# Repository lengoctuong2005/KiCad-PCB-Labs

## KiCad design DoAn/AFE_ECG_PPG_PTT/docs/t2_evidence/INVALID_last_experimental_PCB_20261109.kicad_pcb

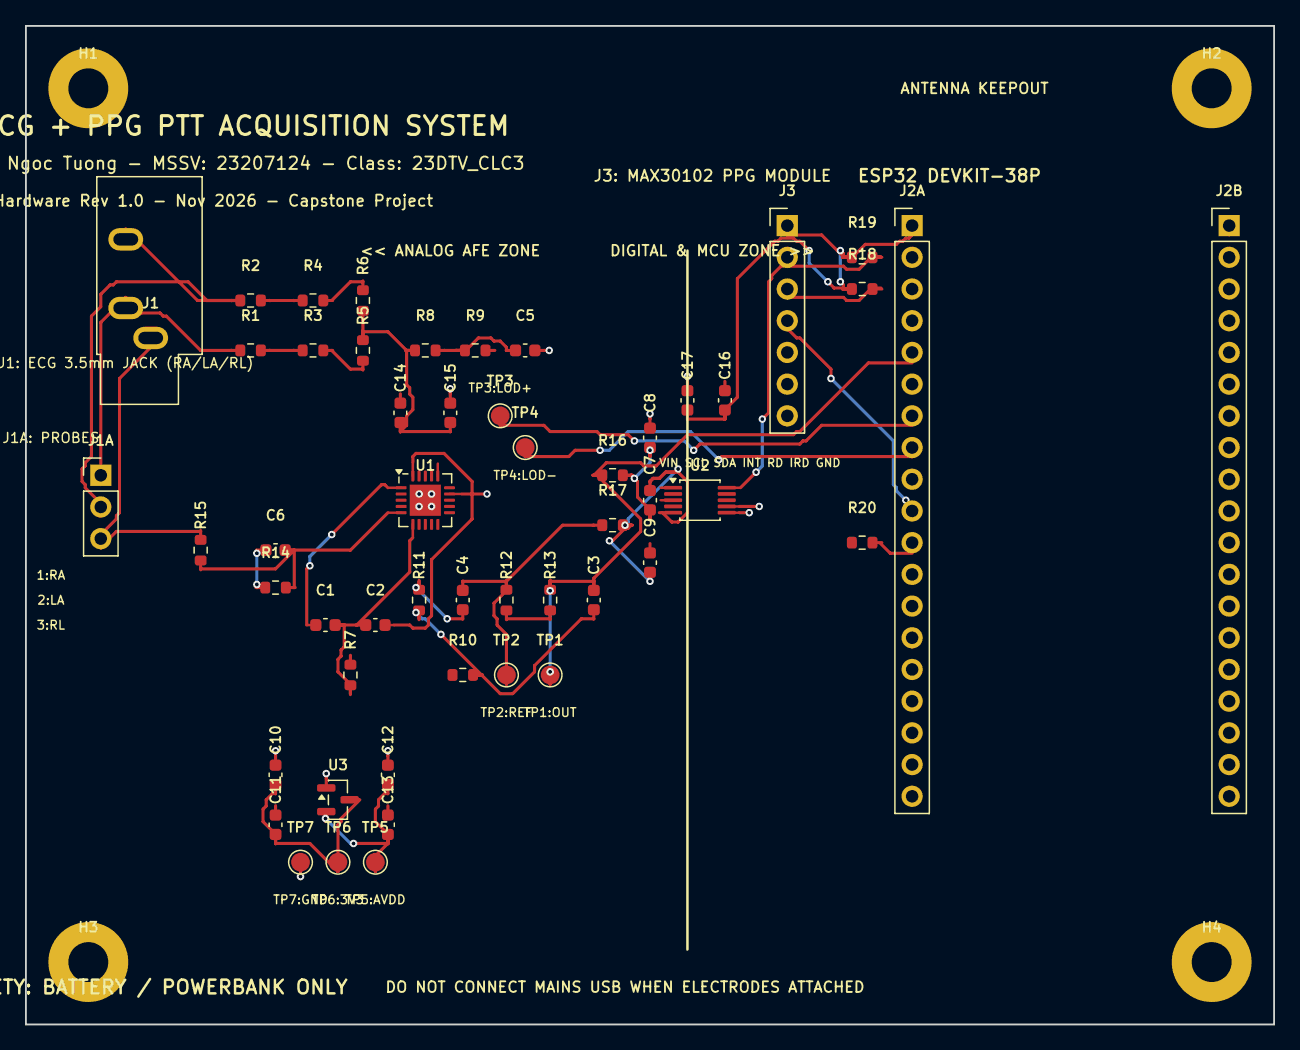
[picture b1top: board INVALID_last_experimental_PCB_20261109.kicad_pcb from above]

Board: 2 copper layers, 100.0 x 80.0 mm, 56 parts (0 on the bottom side), 31 nets.

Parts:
C1, C2: 0.33uF; C_0603_1608Metric
C3: 22nF; C_0603_1608Metric
C4, C7: 10nF; C_0603_1608Metric
C5, C11, C13, C14, C16: 0.1uF; C_0603_1608Metric
C6, C8, C9: 1nF; C_0603_1608Metric
C10, C12, C15, C17: 1uF; C_0603_1608Metric
H1, H2, H3, H4: M3; MountingHole_3.2mm_M3_Pad
J1: SJ1-3533NG; Jack_3.5mm_CUI_SJ1-3533NG_Horizontal
J1A: ECG_PROBES; PinHeader_1x03_P2.54mm_Vertical
J2A: ESP32_L; PinHeader_1x19_P2.54mm_Vertical
J2B: ESP32_R; PinHeader_1x19_P2.54mm_Vertical
J3: MAX30102; PinHeader_1x07_P2.54mm_Vertical
R1, R2, R3, R4: 180k; R_0603_1608Metric
R5, R6, R7, R8, R9: 10M; R_0603_1608Metric
R10, R11, R12: 100k; R_0603_1608Metric
R13, R14: 1M; R_0603_1608Metric
R15: 360k; R_0603_1608Metric
R16, R17: 1k; R_0603_1608Metric
R18, R19: 4.7k; R_0603_1608Metric
R20: 10k; R_0603_1608Metric
TP1: ECG_OUT; TestPoint_Pad_D1.5mm
TP2: REFOUT; TestPoint_Pad_D1.5mm
TP3: LOD+; TestPoint_Pad_D1.5mm
TP4: LOD-; TestPoint_Pad_D1.5mm
TP5: +VS_A; TestPoint_Pad_D1.5mm
TP6: +3V3; TestPoint_Pad_D1.5mm
TP7: GND; TestPoint_Pad_D1.5mm
U1: AD8232ACPZ; LFCSP-20-1EP_4x4mm_P0.5mm_EP2.5x2.5mm
U2: ADS1115IDGST; TSSOP-10_3x3mm_P0.5mm
U3: MCP1700-3002E; SOT-23

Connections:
+3V3: C10.1, C11.1, C16.1, C17.1, J2A.1, J3.1, R18.1, R19.1, R20.1, TP6.1, U2.8, U3.3
+VS_A: C12.1, C13.1, C14.1, C15.1, R5.1, R6.1, R8.1, TP5.1, U1.13, U1.17, U3.2
ADS_ALERT: J2A.11, R20.2, U2.2
AIN0_FILT: C7.1, C8.1, R16.2, U2.4
AIN1_FILT: C7.2, C9.1, R17.2, U2.5
ECG_OUT: C3.2, J2A.5, R13.2, R16.1, TP1.1, U1.10
FR: J2A.9, U1.15
GND: C5.2, C8.2, C9.2, C10.2, C11.2, C12.2, C13.2, C14.2, C15.2, C16.2, C17.2, H1.1, H2.1, H3.1, H4.1, J2A.14, J2B.1, J2B.7, J3.7, R7.2, R9.2, TP7.1, U1.14, U1.16, U1.21, U2.1, U2.3, U2.6, U2.7, U3.1
HPDRIVE: C1.1, U1.1
HPSENSE: C2.2, U1.20
HP_MID: C1.2, C2.1, R7.1, U1.6
I2C_SCL: J2B.3, J3.2, R19.2, U2.10
I2C_SDA: J2B.6, J3.3, R18.2, U2.9
IAOUT: R10.1, U1.19
LA_FILT: R4.2, R6.2, U1.3
LA_INT: R2.2, R4.1
LA_RAW: J1.R, J1A.2, R2.1
LOD+: J2A.7, TP3.1, U1.12
LOD-: J2A.8, TP4.1, U1.11
MAX_INT: J2A.10, J3.4
OPAMP_N: R12.1, R13.1, U1.9
OPAMP_P: C4.1, R11.2, U1.7
RA_FILT: R3.2, R5.2, U1.2
RA_INT: R1.2, R3.1
RA_RAW: J1.T, J1A.1, R1.1
REFIN: C5.1, R8.2, R9.1, U1.18
REFOUT: C4.2, R12.2, R17.1, TP2.1, U1.8
RLDFB: C6.1, R14.1, U1.4
RLD_OUT: C6.2, R14.2, R15.1, U1.5
RL_RAW: J1.S, J1A.3, R15.2
SK_N1: C3.1, R10.2, R11.1

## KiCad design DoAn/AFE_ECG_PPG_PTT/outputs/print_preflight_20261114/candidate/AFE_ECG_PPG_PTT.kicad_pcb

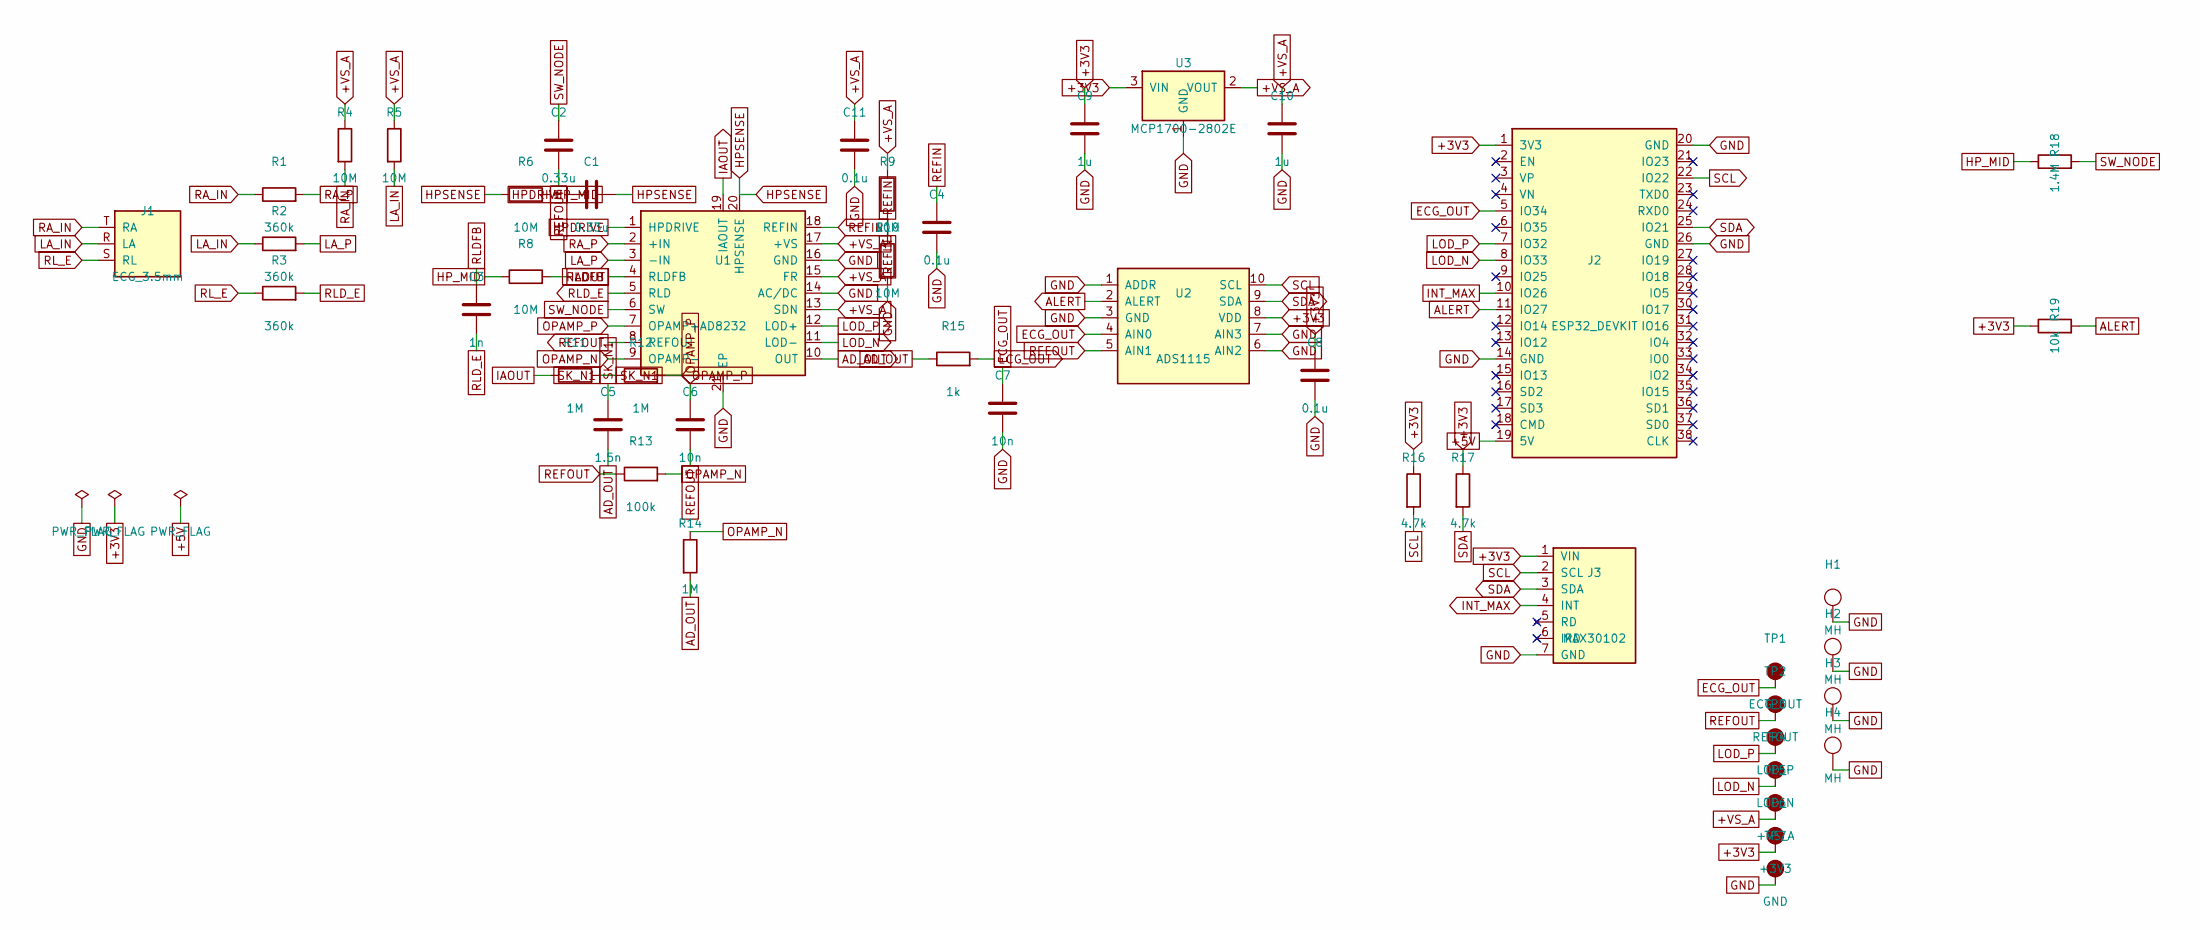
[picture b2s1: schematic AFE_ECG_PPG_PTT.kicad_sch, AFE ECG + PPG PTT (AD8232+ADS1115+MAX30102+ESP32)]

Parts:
C1, C2: 0.33u; C_0603_1608Metric
C3: 1n; C_0603_1608Metric
C4, C8, C11: 0.1u; C_0603_1608Metric
C5: 1.5n; C_0603_1608Metric
C6, C7: 10n; C_0603_1608Metric
C9, C10: 1u; C_0603_1608Metric
H1, H2, H3, H4: MH; MountingHole_3.2mm_M3_Pad
J1: ECG_3.5mm; Jack_3.5mm_CUI_SJ1-3533NG_Horizontal
J2: ESP32_DEVKIT; ESP32_DevKitC_V4_38P
J3: MAX30102; PinHeader_1x07_P2.54mm_Vertical
R1, R2, R3: 360k; R_0603_1608Metric
R4, R5, R6, R8, R9, R10: 10M; R_0603_1608Metric
R11, R12, R14: 1M; R_0603_1608Metric
R13: 100k; R_0603_1608Metric
R15: 1k; R_0603_1608Metric
R16, R17: 4.7k; R_0603_1608Metric
R18: 1.4M; R_0603_1608Metric
R19: 10k; R_0603_1608Metric
TP1: ECG_OUT; TestPoint_Pad_D1.5mm
TP2: REFOUT; TestPoint_Pad_D1.5mm
TP3: LOD_P; TestPoint_Pad_D1.5mm
TP4: LOD_N; TestPoint_Pad_D1.5mm
TP5: +VS_A; TestPoint_Pad_D1.5mm
TP6: +3V3; TestPoint_Pad_D1.5mm
TP7: GND; TestPoint_Pad_D1.5mm
U1: AD8232; LFCSP-20-1EP_4x4mm_P0.5mm_EP2.6x2.6mm
U2: ADS1115; TSSOP-10_3x3mm_P0.5mm
U3: MCP1700-2802E; SOT-23

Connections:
+3V3: C8.1, C9.1, J2.1 (3V3), J3.1 (VIN), R16.1, R17.1, R19.1, TP6.1, U2.8 (VDD), U3.3 (VIN)
+5V: J2.19 (5V)
+VS_A: C10.1, C11.1, R4.1, R5.1, R9.1, TP5.1, U1.13 (SDN), U1.15 (FR), U1.17 (+VS), U3.2 (VOUT)
AD_OUT: C5.2, R14.2, R15.1, U1.10 (OUT)
ALERT: J2.11 (IO27), R19.2, U2.2 (ALERT)
ECG_OUT: C7.1, J2.5 (IO34), R15.2, TP1.1, U2.4 (AIN0)
GND: C4.2, C7.2, C8.2, C9.2, C10.2, C11.2, H1.1, H2.1, H3.1, H4.1, J2.14 (GND), J2.20 (GND), J2.26 (GND), J3.7 (GND), R10.2, TP7.1, U1.14 (AC/DC), U1.16 (GND), U1.21 (EP), U2.1 (ADDR), U2.3 (GND), U2.6 (AIN2), U2.7 (AIN3), U3.1 (GND)
HPDRIVE: C1.1, U1.1 (HPDRIVE)
HPSENSE: C1.2, R6.1, U1.20 (HPSENSE)
HP_MID: R6.2, R8.1, R18.1
IAOUT: R8.2, R11.1, U1.19 (IAOUT)
INT_MAX: J2.10 (IO26), J3.4 (INT)
LA_IN: J1.R (LA), R2.1, R5.2
LA_P: R2.2, U1.3 (-IN)
LOD_N: J2.8 (IO33), TP4.1, U1.11 (LOD-)
LOD_P: J2.7 (IO32), TP3.1, U1.12 (LOD+)
OPAMP_N: R13.2, R14.1, U1.9 (OPAMP-)
OPAMP_P: C6.1, R12.2, U1.7 (OPAMP+)
RA_IN: J1.T (RA), R1.1, R4.2
RA_P: R1.2, U1.2 (+IN)
REFIN: C4.1, R9.2, R10.1, U1.18 (REFIN)
REFOUT: C2.2, C6.2, R13.1, TP2.1, U1.8 (REFOUT), U2.5 (AIN1)
RLDFB: C3.1, U1.4 (RLDFB)
RLD_E: C3.2, R3.2, U1.5 (RLD)
RL_E: J1.S (RL), R3.1
SCL: J2.22 (IO22), J3.2 (SCL), R16.2, U2.10 (SCL)
SDA: J2.25 (IO21), J3.3 (SDA), R17.2, U2.9 (SDA)
SK_N1: C5.1, R11.2, R12.1
SW_NODE: C2.1, R18.2, U1.6 (SW)

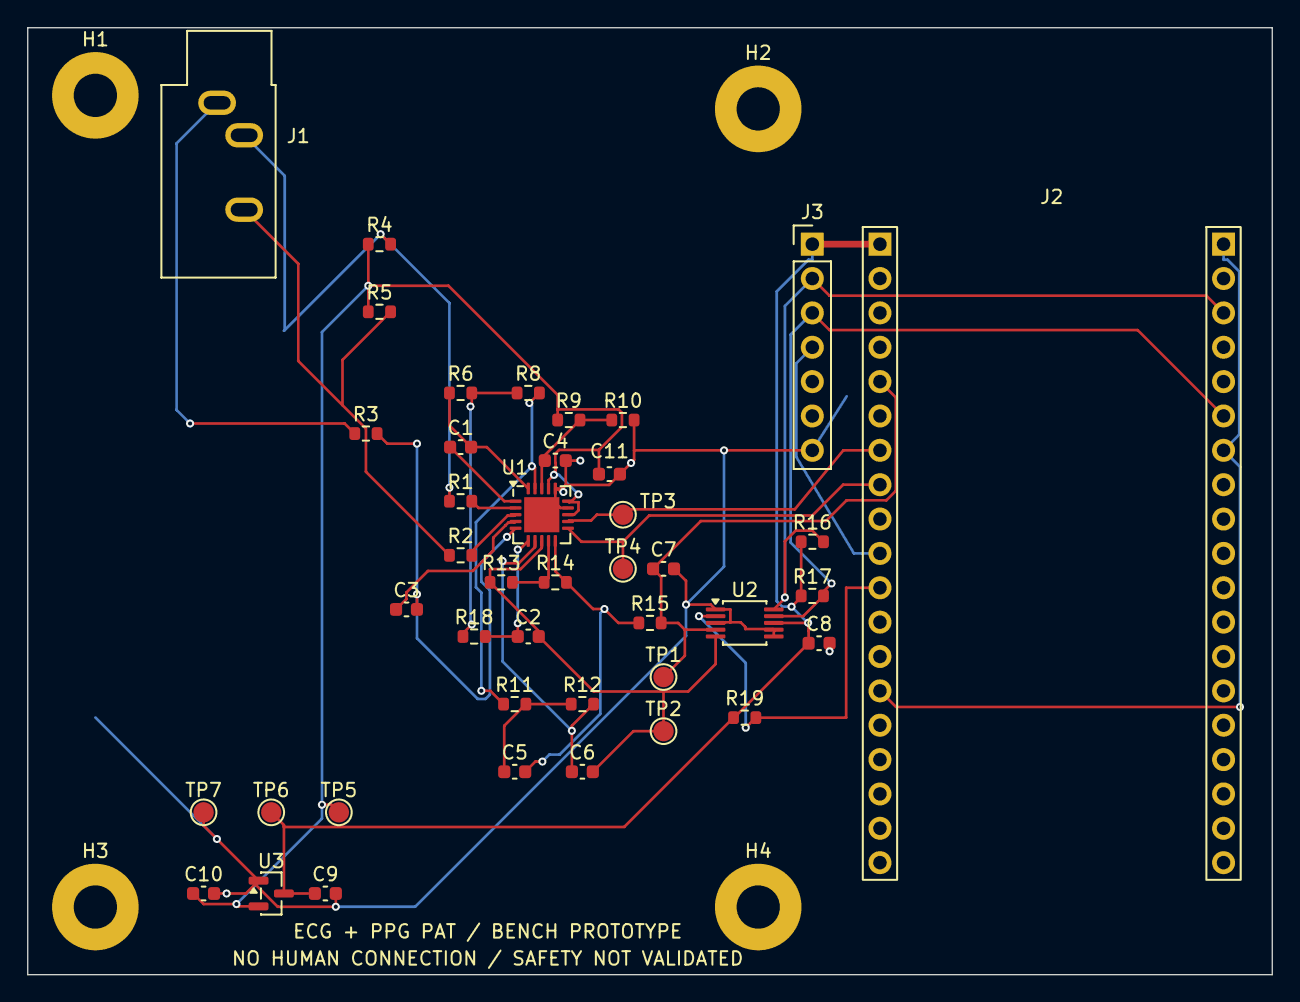
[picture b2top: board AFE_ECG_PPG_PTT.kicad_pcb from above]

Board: 2 copper layers, 92.0 x 70.0 mm, 46 parts (0 on the bottom side), 28 nets.

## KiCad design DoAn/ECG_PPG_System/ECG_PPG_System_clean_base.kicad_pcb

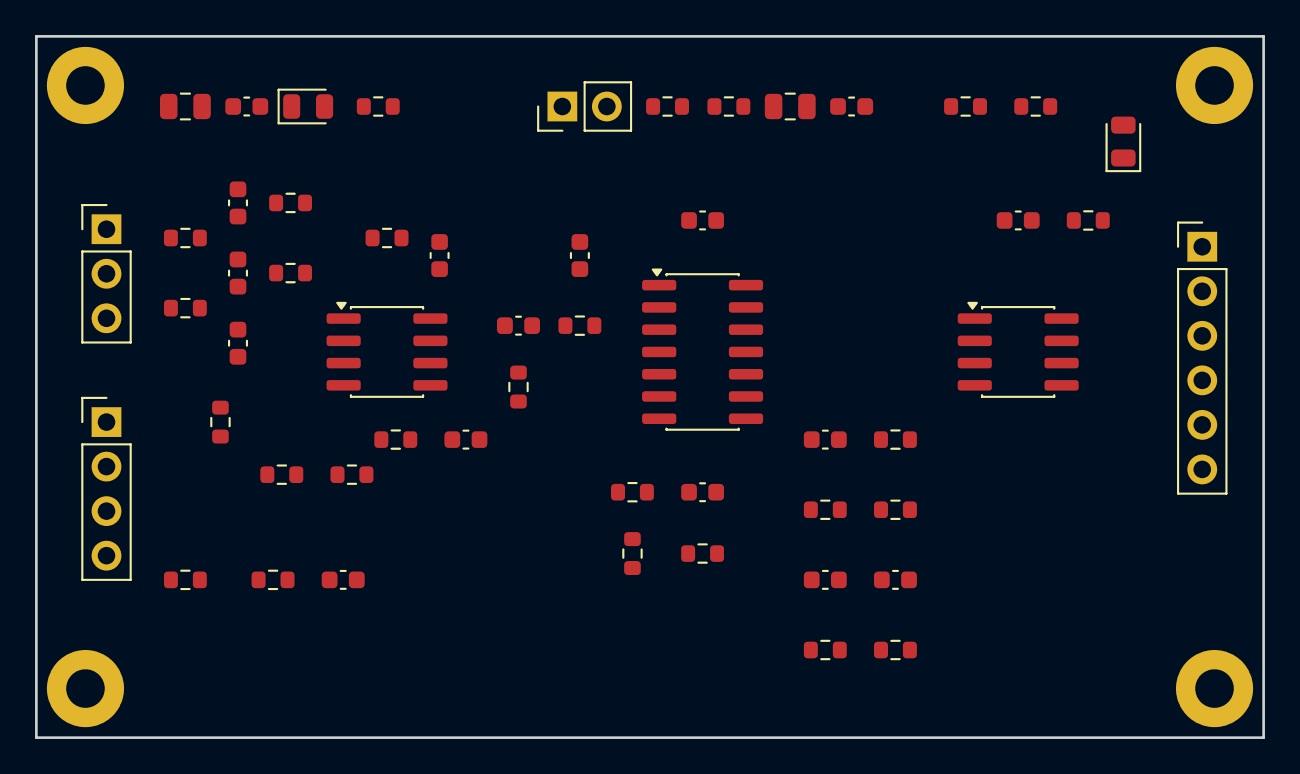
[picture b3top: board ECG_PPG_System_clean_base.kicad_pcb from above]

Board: 2 copper layers, 70.0 x 40.0 mm, 58 parts (0 on the bottom side), 31 nets, no tracks yet.

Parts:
C1, C3: 10uF; C_0805_2012Metric
C2, C4, C8, C11, C13, C18: 100nF; C_0603_1608Metric
C5: 100pF; C_0603_1608Metric
C6, C7: 47pF; C_0603_1608Metric
C9: 1nF; C_0603_1608Metric
C10, C15, C16: 1uF; C_0603_1608Metric
C12: 47nF; C_0603_1608Metric
C14: 22pF; C_0603_1608Metric
C17: 470nF; C_0603_1608Metric
D1: Green_PWR; LED_0805_2012Metric
D2: Red_PULSE; LED_0805_2012Metric
H1, H2, H3, H4: M2; MountingHole_2.2mm_M2_Pad
J1: Power_In; PinHeader_1x02_P2.54mm_Vertical
J2: ECG_Leads; PinHeader_1x03_P2.54mm_Vertical
J3: PPG_Sensor; PinHeader_1x04_P2.54mm_Vertical
J4: System_Out; PinHeader_1x06_P2.54mm_Vertical
R1, R2, R9, R10, R25: 100k; R_0603_1608Metric
R3, R4, R5, R8, R23, R27: 1k; R_0603_1608Metric
R6, R7: 10M; R_0603_1608Metric
R11, R18: 1M; R_0603_1608Metric
R12: 390k; R_0603_1608Metric
R13, R20: 330k; R_0603_1608Metric
R14, R15: 39k; R_0603_1608Metric
R16, R26: 10k; R_0603_1608Metric
R17: 91k; R_0603_1608Metric
R19: 220R; R_0603_1608Metric
R21, R22: 15k; R_0603_1608Metric
R24: 47k; R_0603_1608Metric
U1: AD623ARZ; SOIC-8_3.9x4.9mm_P1.27mm
U2: MCP6004-E/SL; SOIC-14_3.9x8.7mm_P1.27mm
U3: MCP6002-E/SN; SOIC-8_3.9x4.9mm_P1.27mm

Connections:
DRL_CM: C9.1, R9.2, R10.2, R11.1, U2.5
DRL_OUT: C9.2, R11.2, R12.1, U2.7
ECG_FB: R16.1, R17.1, U2.9
ECG_HPF_OUT: C10.2, R13.1, R14.1
ECG_IA_OUT: C10.1, U1.6
ECG_LPF_IN: C12.1, R15.2, U2.10
ECG_LPF_NODE: C11.1, R14.2, R15.1
ECG_OUT: C11.2, J4.3, R17.2, U2.8
GND: C1.2, C2.2, C3.2, C4.2, C6.2, C7.2, C8.2, C13.2, C18.2, D1.1, D2.1, H1.1, H2.1, H3.1, H4.1, J1.2, J3.4, J4.2, R2.2, R26.2, U1.4, U2.11, U3.4
LA_FILT: C5.2, C7.1, R5.2, R7.1, R10.1, U1.3
LA_RAW: J2.2, R5.1
LED_DRV: J3.2, R19.2
NET_D1_R3: D1.2, R3.2
NET_D2_R27: D2.2, R27.2
PD_ANODE: C14.1, J3.3, R18.1, U2.12
PPG_FB: R23.1, R24.1, U3.2
PPG_HPF_OUT: C15.2, R20.1, R21.1
PPG_LPF_IN: C17.1, R22.2, U3.3
PPG_LPF_NODE: C16.1, R21.2, R22.1
PPG_OUT: C16.2, J4.4, R24.2, U3.1, U3.5
PPG_TIA_OUT: C14.2, C15.1, R18.2, U2.14
PULSE_TRIG: J4.5, R27.1, U3.7
RA_FILT: C5.1, C6.1, R4.2, R6.1, R9.1, U1.2
RA_RAW: J2.1, R4.1
RG1: R8.1, U1.1
RG2: R8.2, U1.8
RL_DRL: J2.3, R12.2
VCC: C1.1, C2.1, C8.1, C13.1, C18.1, J1.1, J3.1, J4.1, R1.1, R3.1, R19.1, U1.7, U2.4, U3.8
VMID: C3.1, C4.1, R1.2, R2.1, U2.3
VREF: C12.2, C17.2, J4.6, R6.2, R7.2, R13.2, R16.2, R20.2, R23.2, R25.1, U1.5, U2.1, U2.2, U2.6, U2.13
VREF_THR: R25.2, R26.1, U3.6

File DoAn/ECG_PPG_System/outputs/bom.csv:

"Refs","Value","Footprint","Qty","DNP"
"C1","10uF","Capacitor_SMD:C_0805_2012Metric","1",""
"C2","100nF","Capacitor_SMD:C_0603_1608Metric","1",""
"C3","10uF","Capacitor_SMD:C_0805_2012Metric","1",""
"C4","100nF","Capacitor_SMD:C_0603_1608Metric","1",""
"C5","100pF","Capacitor_SMD:C_0603_1608Metric","1",""
"C6","47pF","Capacitor_SMD:C_0603_1608Metric","1",""
"C7","47pF","Capacitor_SMD:C_0603_1608Metric","1",""
"C8","100nF","Capacitor_SMD:C_0603_1608Metric","1",""
"C9","1nF","Capacitor_SMD:C_0603_1608Metric","1",""
"C10","1uF","Capacitor_SMD:C_0603_1608Metric","1",""
"C11","100nF","Capacitor_SMD:C_0603_1608Metric","1",""
"C12","47nF","Capacitor_SMD:C_0603_1608Metric","1",""
"C13","100nF","Capacitor_SMD:C_0603_1608Metric","1",""
"C14","22pF","Capacitor_SMD:C_0603_1608Metric","1",""
"C15","1uF","Capacitor_SMD:C_0603_1608Metric","1",""
"C16","1uF","Capacitor_SMD:C_0603_1608Metric","1",""
"C17","470nF","Capacitor_SMD:C_0603_1608Metric","1",""
"C18","100nF","Capacitor_SMD:C_0603_1608Metric","1",""
"D1","Green_PWR","LED_SMD:LED_0805_2012Metric","1",""
"D2","Red_PULSE","LED_SMD:LED_0805_2012Metric","1",""
"J1","Power_In","Connector_PinHeader_2.54mm:PinHeader_1x02_P2.54mm_Vertical","1",""
"J2","ECG_Leads","Connector_PinHeader_2.54mm:PinHeader_1x03_P2.54mm_Vertical","1",""
"J3","PPG_Sensor","Connector_PinHeader_2.54mm:PinHeader_1x04_P2.54mm_Vertical","1",""
"J4","System_Out","Connector_PinHeader_2.54mm:PinHeader_1x06_P2.54mm_Vertical","1",""
"R1","100k","Resistor_SMD:R_0603_1608Metric","1",""
"R2","100k","Resistor_SMD:R_0603_1608Metric","1",""
"R3","1k","Resistor_SMD:R_0603_1608Metric","1",""
"R4","1k","Resistor_SMD:R_0603_1608Metric","1",""
"R5","1k","Resistor_SMD:R_0603_1608Metric","1",""
"R6","10M","Resistor_SMD:R_0603_1608Metric","1",""
"R7","10M","Resistor_SMD:R_0603_1608Metric","1",""
"R8","1k","Resistor_SMD:R_0603_1608Metric","1",""
"R9","100k","Resistor_SMD:R_0603_1608Metric","1",""
"R10","100k","Resistor_SMD:R_0603_1608Metric","1",""
"R11","1M","Resistor_SMD:R_0603_1608Metric","1",""
"R12","390k","Resistor_SMD:R_0603_1608Metric","1",""
"R13","330k","Resistor_SMD:R_0603_1608Metric","1",""
"R14","39k","Resistor_SMD:R_0603_1608Metric","1",""
"R15","39k","Resistor_SMD:R_0603_1608Metric","1",""
"R16","10k","Resistor_SMD:R_0603_1608Metric","1",""
"R17","91k","Resistor_SMD:R_0603_1608Metric","1",""
"R18","1M","Resistor_SMD:R_0603_1608Metric","1",""
"R19","220R","Resistor_SMD:R_0603_1608Metric","1",""
"R20","330k","Resistor_SMD:R_0603_1608Metric","1",""
"R21","15k","Resistor_SMD:R_0603_1608Metric","1",""
"R22","15k","Resistor_SMD:R_0603_1608Metric","1",""
"R23","1k","Resistor_SMD:R_0603_1608Metric","1",""
"R24","47k","Resistor_SMD:R_0603_1608Metric","1",""
"R25","100k","Resistor_SMD:R_0603_1608Metric","1",""
"R26","10k","Resistor_SMD:R_0603_1608Metric","1",""
"R27","1k","Resistor_SMD:R_0603_1608Metric","1",""
"U1","AD623ARZ","Package_SO:SOIC-8_3.9x4.9mm_P1.27mm","1",""
"U2","MCP6004-E/SL","Package_SO:SOIC-14_3.9x8.7mm_P1.27mm","1",""
"U3","MCP6002-E/SN","Package_SO:SOIC-8_3.9x4.9mm_P1.27mm","1",""

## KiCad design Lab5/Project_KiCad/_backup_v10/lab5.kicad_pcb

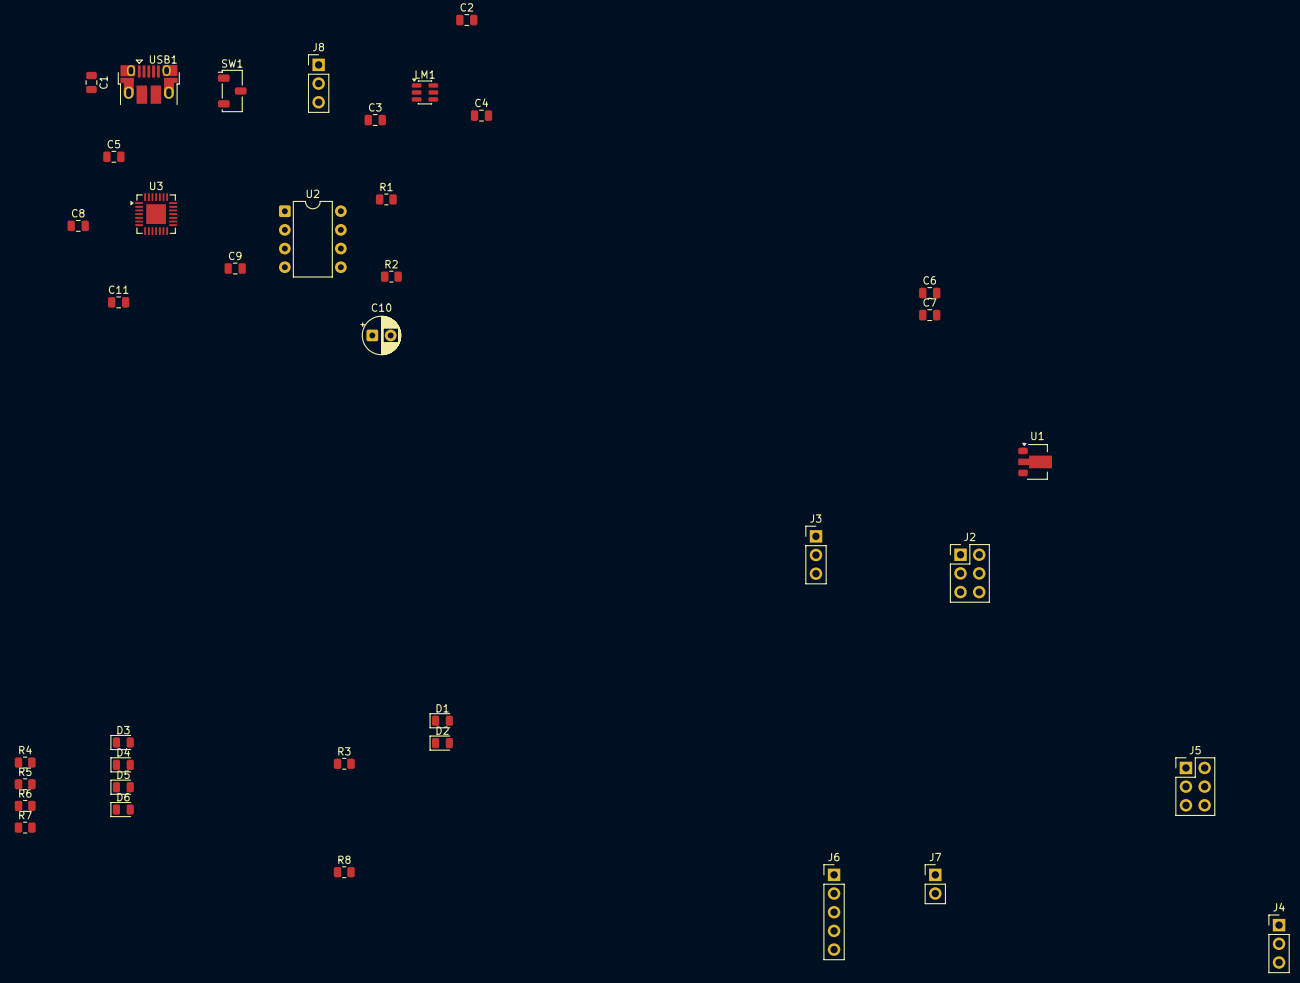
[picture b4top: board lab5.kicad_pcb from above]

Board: 2 copper layers, 38 parts (0 on the bottom side), 29 nets, no tracks yet.

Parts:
C1, C2, C3, C6, C7: 2.2uF; C_0805_2012Metric
C4: 1uF; C_0805_2012Metric
C5, C8, C11: 100nF; C_0805_2012Metric
C9: 10nF; C_0805_2012Metric
C10: 10uF; CP_Radial_D5.0mm_P2.50mm
D1: TX1; LED_0805_2012Metric
D2: RX1; LED_0805_2012Metric
D3: 5V; LED_0805_2012Metric
D4: 3V3; LED_0805_2012Metric
D5: -VDD; LED_0805_2012Metric
D6: 1Hz; LED_0805_2012Metric
J2, J5: Connector 3x2; PinHeader_2x03_P2.54mm_Vertical
J3, J4: Jumper_Dual_1x3; PinHeader_1x03_P2.54mm_Vertical
J6: Connector_1x5; PinHeader_1x05_P2.54mm_Vertical
J7: Connector_1x2; PinHeader_1x02_P2.54mm_Vertical
J8: Conn_01x03; PinHeader_1x03_P2.54mm_Vertical
LM1: SOT-23-6
R1: 47k; R_0805_2012Metric
R2: 100k; R_0805_2012Metric
R3, R4, R5, R6, R7, R8: 1k; R_0805_2012Metric
SW1: ON/OFF SWITCH; Nidec_Copal_CAS-120A
U1: AMS1117-3V3; SOT-89-3
U2: NE555; DIP-8_W7.62mm
U3: CP2102; QFN-28-1EP_5x5mm_P0.5mm_EP2.7x2.7mm
USB1: USB_Micro-B_Amphenol_10103594-0001LF_Horizontal

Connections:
/1Hz: J7.2, R7.2, U2.3 (Q)
/D+: U3.4 (D+), USB1.3 (D+/DM)
/D-: U3.5 (D-), USB1.2 (D-/DM)
/DTR: C5.1, J6.4
/P1+: J2.1, J2.2, J2.3, J3.2
/P1-: J2.4, J2.5, J2.6
/P2+: J4.2, J5.1, J5.2, J5.3
/P2-: J5.4, J5.5, J5.6
/RX: D2.1 (K), J6.2, U3.25 (RXD)
/TX: D1.1 (K), J6.3, U3.26 (TXD)
/VDD_3V3: C7.2, J3.3, J4.3, J6.1, R5.2, U1.2 (Vout)
/VDD_5V: C6.2, C11.2, J3.1, J4.1, R1.1, R3.1, R4.2, R8.1, SW1.2, U1.3 (Vin), U2.4 (R), U2.8 (VCC), U3.7 (REGIN), U3.8 (VBUS)
GND: C1.2, C2.2, C3.2, C6.1, C7.1, C8.1, C9.2, C10.2, C11.1, D3.1 (K), D4.1 (K), D5.2 (A), D6.1 (K), J6.5, J7.1, LM1.2 (GND), U1.1, U2.1 (GND), U3.3 (GND), USB1.5 (GND), USB1.6
unnamed: D1.2 (A), R3.2
unnamed: D2.2 (A), R8.2
unnamed: D3.2 (A), R4.1
unnamed: D4.2 (A), R5.1
unnamed: D5.1 (K), R6.1
unnamed: D6.2 (A), R7.1
unnamed: C3.1, J8.2, LM1.4 (EN)
unnamed: C4.2, LM1.5 (C1+)
unnamed: C4.1, LM1.6 (C1-)
unnamed: C2.1, LM1.1 (VOUT)
unnamed: C9.1, U2.5 (CV)
unnamed: R1.2, R2.1, U2.7 (DC)
unnamed: C10.1, R2.2, U2.2 (TR), U2.6 (TH)
unnamed: C5.2, U3.28 (DTR)
unnamed: C8.2, U3.6 (VDD)
unnamed: C1.1, USB1.1 (VBUS)

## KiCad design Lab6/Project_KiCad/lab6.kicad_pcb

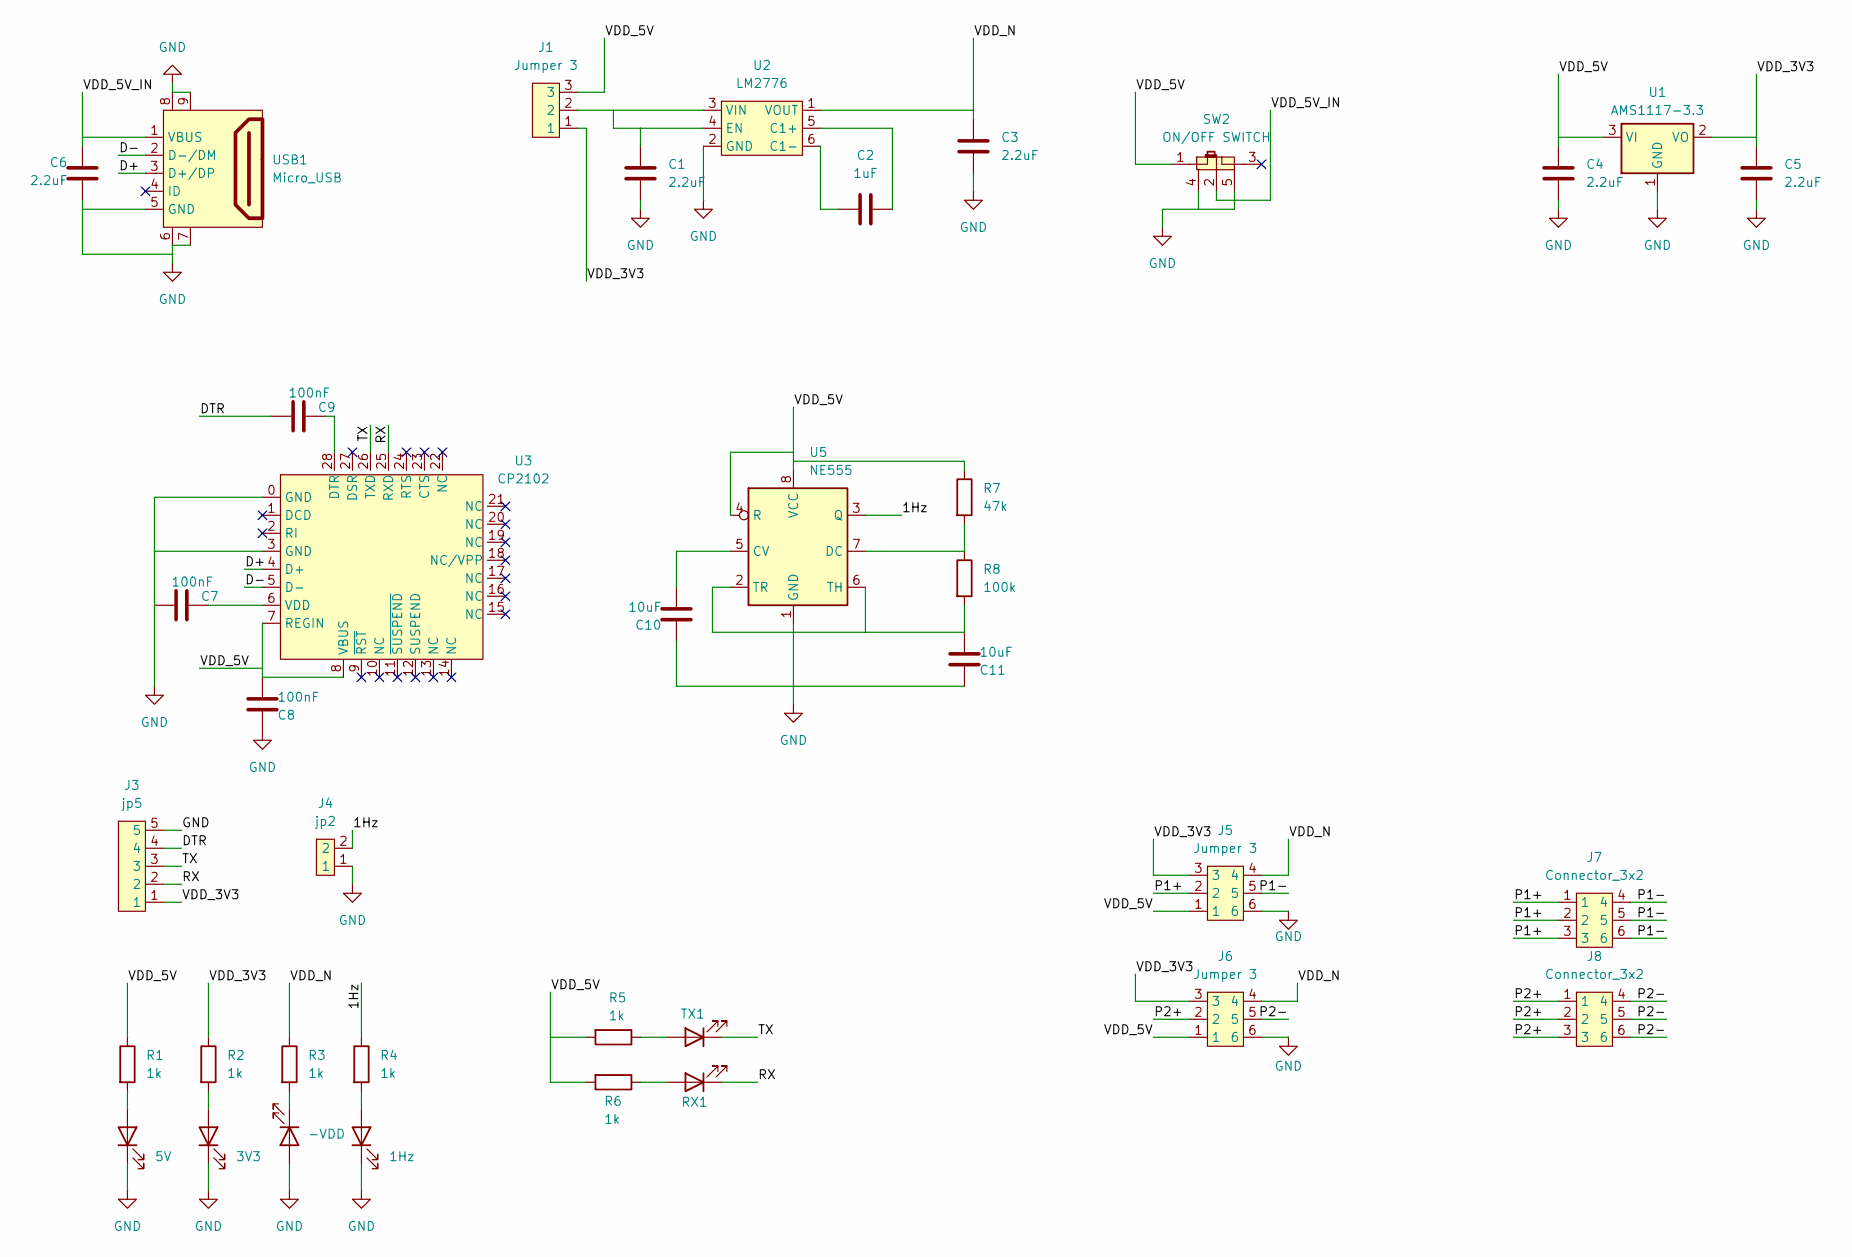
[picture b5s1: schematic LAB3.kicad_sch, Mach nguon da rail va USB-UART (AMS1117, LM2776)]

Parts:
C1, C3, C4, C5, C6: 2.2uF; C_0805_2012Metric
C2: 1uF; C_0805_2012Metric
C7, C8, C9: 100nF; C_0805_2012Metric
C10, C11: 10uF; CP_Radial_D5.0mm_P2.50mm
D1: 5V; LED_0805_2012Metric
D2: 3V3; LED_0805_2012Metric
D3: -VDD; LED_0805_2012Metric
D4: 1Hz; LED_0805_2012Metric
D5: RX1; LED_0805_2012Metric
D6: TX1; LED_0805_2012Metric
J1: Jumper 3; PinHeader_1x03_P2.54mm_Vertical
J3: jp5; PinHeader_1x05_P2.54mm_Vertical
J4: jp2; PinHeader_1x02_P2.54mm_Vertical
J5, J6: Jumper 3
J7, J8: Connector_3x2; Connector 3x2
R1, R2, R3, R4, R5, R6: 1k; R_0805_2012Metric
R7: 47k; R_0805_2012Metric
R8: 100k; R_0805_2012Metric
SW2: ON/OFF SWITCH; SWITCH_ON_OFF
U1: AMS1117-3.3; SOT-223-3_TabPin2
U2: LM2776; SOT-23-6
U3: CP2102
U5: NE555; SO-8_3.9x4.9mm_P1.27mm
USB1: Micro_USB

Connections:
/1Hz: J4.2, R4.1, U5.3 (Q)
/D+: U3.4 (D+), USB1.3 (D+/DP)
/D-: U3.5 (D-), USB1.2 (D-/DM)
/DTR: C9.1, J3.4
/P1+: J5.2, J7.1, J7.2, J7.3
/P1-: J5.5, J7.4, J7.5, J7.6
/P2+: J6.2, J8.1, J8.2, J8.3
/P2-: J6.5, J8.4, J8.5, J8.6
/RX: D5.1 (K), J3.2, U3.25 (RXD)
/TX: D6.1 (K), J3.3, U3.26 (TXD)
/VDD_3V3: C5.1, J1.1, J3.1, J5.3, J6.3, R2.1, U1.2 (VO)
/VDD_5V: C4.1, C8.2, J1.3, J5.1, J6.1, R1.1, R5.2, R6.2, R7.1, SW2.1, U1.3 (VI), U3.7 (REGIN), U3.8 (VBUS), U5.4 (R), U5.8 (VCC)
/VDD_5V_IN: C6.1, SW2.2, USB1.1 (VBUS)
/VDD_N: C3.1, J5.4, J6.4, R3.1, U2.1 (VOUT)
GND: C1.2, C3.2, C4.2, C5.2, C6.2, C7.1, C8.1, C10.1, C11.1, D1.1 (K), D2.1 (K), D3.2 (A), D4.1 (K), J3.5, J4.1, J5.6, J6.6, SW2.4, SW2.5, U1.1 (GND), U2.2 (GND), U3.0 (GND), U3.3 (GND), U5.1 (GND), USB1.5 (GND), USB1.6, USB1.7, USB1.8, USB1.9
unnamed: D1.2 (A), R1.2
unnamed: D2.2 (A), R2.2
unnamed: D3.1 (K), R3.2
unnamed: D4.2 (A), R4.2
unnamed: D5.2 (A), R6.1
unnamed: D6.2 (A), R5.1
unnamed: C2.2, U2.5 (C1+)
unnamed: C2.1, U2.6 (C1-)
unnamed: C1.1, J1.2, U2.3 (VIN), U2.4 (EN)
unnamed: C9.2, U3.28 (DTR)
unnamed: C7.2, U3.6 (VDD)
unnamed: C10.2, U5.5 (CV)
unnamed: R7.2, R8.1, U5.7 (DC)
unnamed: C11.2, R8.2, U5.2 (TR), U5.6 (TH)

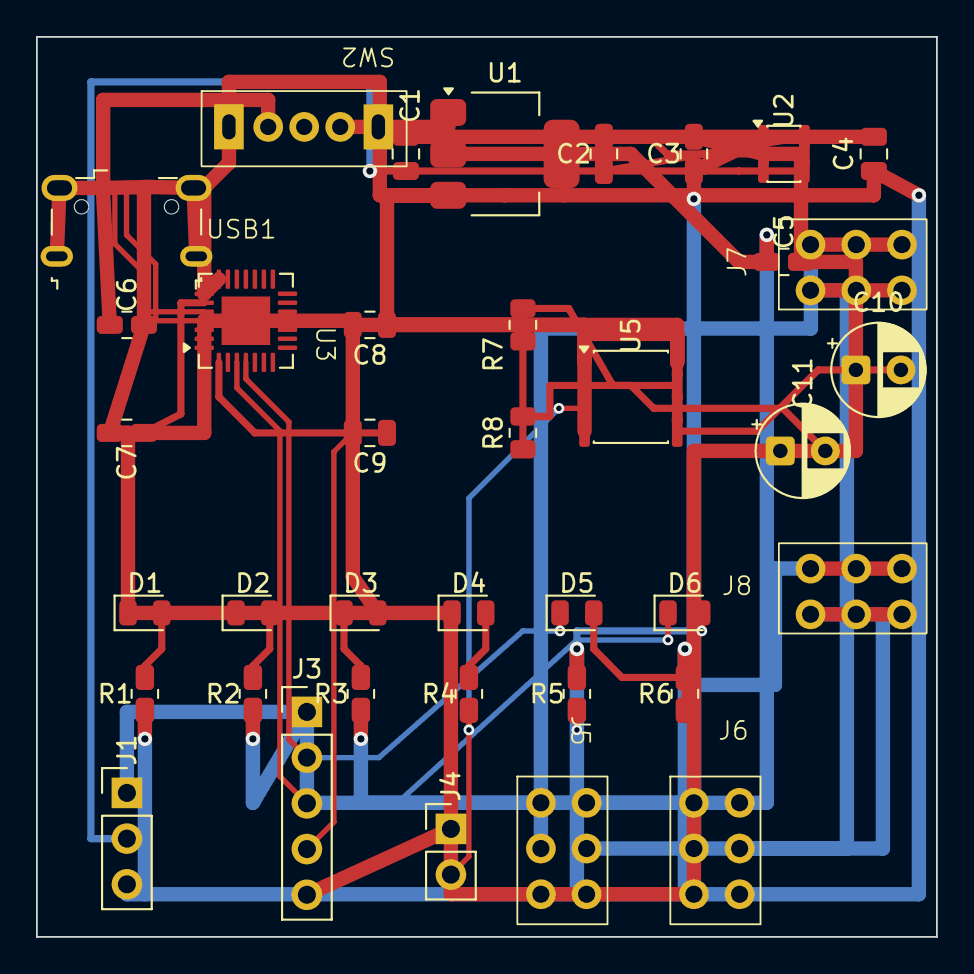
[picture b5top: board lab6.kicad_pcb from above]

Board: 2 copper layers, 50.0 x 50.0 mm, 38 parts (0 on the bottom side), 29 nets.

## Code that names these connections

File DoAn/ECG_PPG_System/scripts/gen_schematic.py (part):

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    elements.append(label("GND", 25.40-5.08, 25.40-1.27))

    elements.append(sym_inst("ecg_ppg:Conn_01x03", "J2", "ECG_Leads", "Connector_PinHeader_2.54mm:PinHeader_1x03_P2.54mm_Vertical", 25.40, 76.20, ["1", "2", "3"]))
    elements.append(label("RA_RAW", 25.40-5.08, 76.20+2.54))
    elements.append(label("LA_RAW", 25.40-5.08, 76.20+0.00))
    elements.append(label("RL_DRL", 25.40-5.08, 76.20-2.54))

    elements.append(sym_inst("ecg_ppg:Conn_01x04", "J3", "PPG_Sensor", "Connector_PinHeader_2.54mm:PinHeader_1x04_P2.54mm_Vertical", 25.40, 127.00, ["1", "2", "3", "4"]))
    elements.append(label("VCC", 25.40-5.08, 127.00+3.81))
    elements.append(label("LED_DRV", 25.40-5.08, 127.00+1.27))
    elements.append(label("PD_ANODE", 25.40-5.08, 127.00-1.27))
    elements.append(label("GND", 25.40-5.08, 127.00-3.81))

    elements.append(sym_inst("ecg_ppg:Conn_01x06", "J4", "System_Out", "Connector_PinHeader_2.54mm:PinHeader_1x06_P2.54mm_Vertical", 355.60, 76.20, ["1", "2", "3", "4", "5", "6"]))
    elements.append(label("VCC", 355.60-5.08, 76.20+6.35))
    elements.append(label("GND", 355.60-5.08, 76.20+3.81))
    elements.append(label("ECG_OUT", 355.60-5.08, 76.20+1.27))
    elements.append(label("PPG_OUT", 355.60-5.08, 76.20-1.27))
    elements.append(label("PULSE_TRIG", 355.60-5.08, 76.20-3.81))
    elements.append(label("VREF", 355.60-5.08, 76.20-6.35))

    # 2. ICs
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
